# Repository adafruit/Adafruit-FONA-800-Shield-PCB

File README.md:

## Adafruit FONA 800 Shield PCB

<a href="http://www.adafruit.com/products/2468"><br/>
Click here to purchase one from the Adafruit shop</a>

PCB files for the Adafruit FONA 800 Shield. Format is EagleCAD schematic and board layout
* https://www.adafruit.com/products/2468

### DESCRIPTION
Ring, Ring! Who's that callin'? It's your microcontroller! Introducing Adafruit FONA 800 Shield, an adorable all-in-one cellular phone shield that lets you add voice, text, SMS and data to your project in an easy to use pluggable shield.

This shield fits on top of any classic Arduino or compatible, and packs a surprising amount of technology into it's little frame. At the heart is a GSM cellular module (we use the latest SIM800) the size of a postage stamp. This module can do just about everything. 

If you want a Shield Version with GPS, check out the Adafruit FONA 808 Shield - Mini Cellular GSM + GPS for Arduino [click here](https://www.adafruit.com/product/2636).

If you just want a plain FONA breakout, [click here](https://www.adafruit.com/product/1946).

Quad-band 850/900/1800/1900MHz - connect onto any global GSM network with any 2G SIM (in the USA, T-Mobile is suggested)
Make and receive voice calls using a headset OR an external 8Ω speaker + electret microphone
Send and receive SMS messages
Send and receive GPRS data (TCP/IP, HTTP, etc.)
Scan and receive FM radio broadcasts (yeah, we don't exactly know why this was included but it works really well)
PWM/Buzzer vibrational motor control
AT command interface with "auto baud" detection
Sounds delicious, right? So we plated this fine module onto a shield with all the extras you need to make your next project shine.

### License

Adafruit invests time and resources providing this open source design, please support Adafruit and open-source hardware by purchasing products from [Adafruit.com](https://www.adafruit.com)!

Designed by Adafruit Industries. 

Creative Commons Attribution, Share-Alike license, check license.txt for more information All text above must be included in any redistribution - 
See license.txt for more information.

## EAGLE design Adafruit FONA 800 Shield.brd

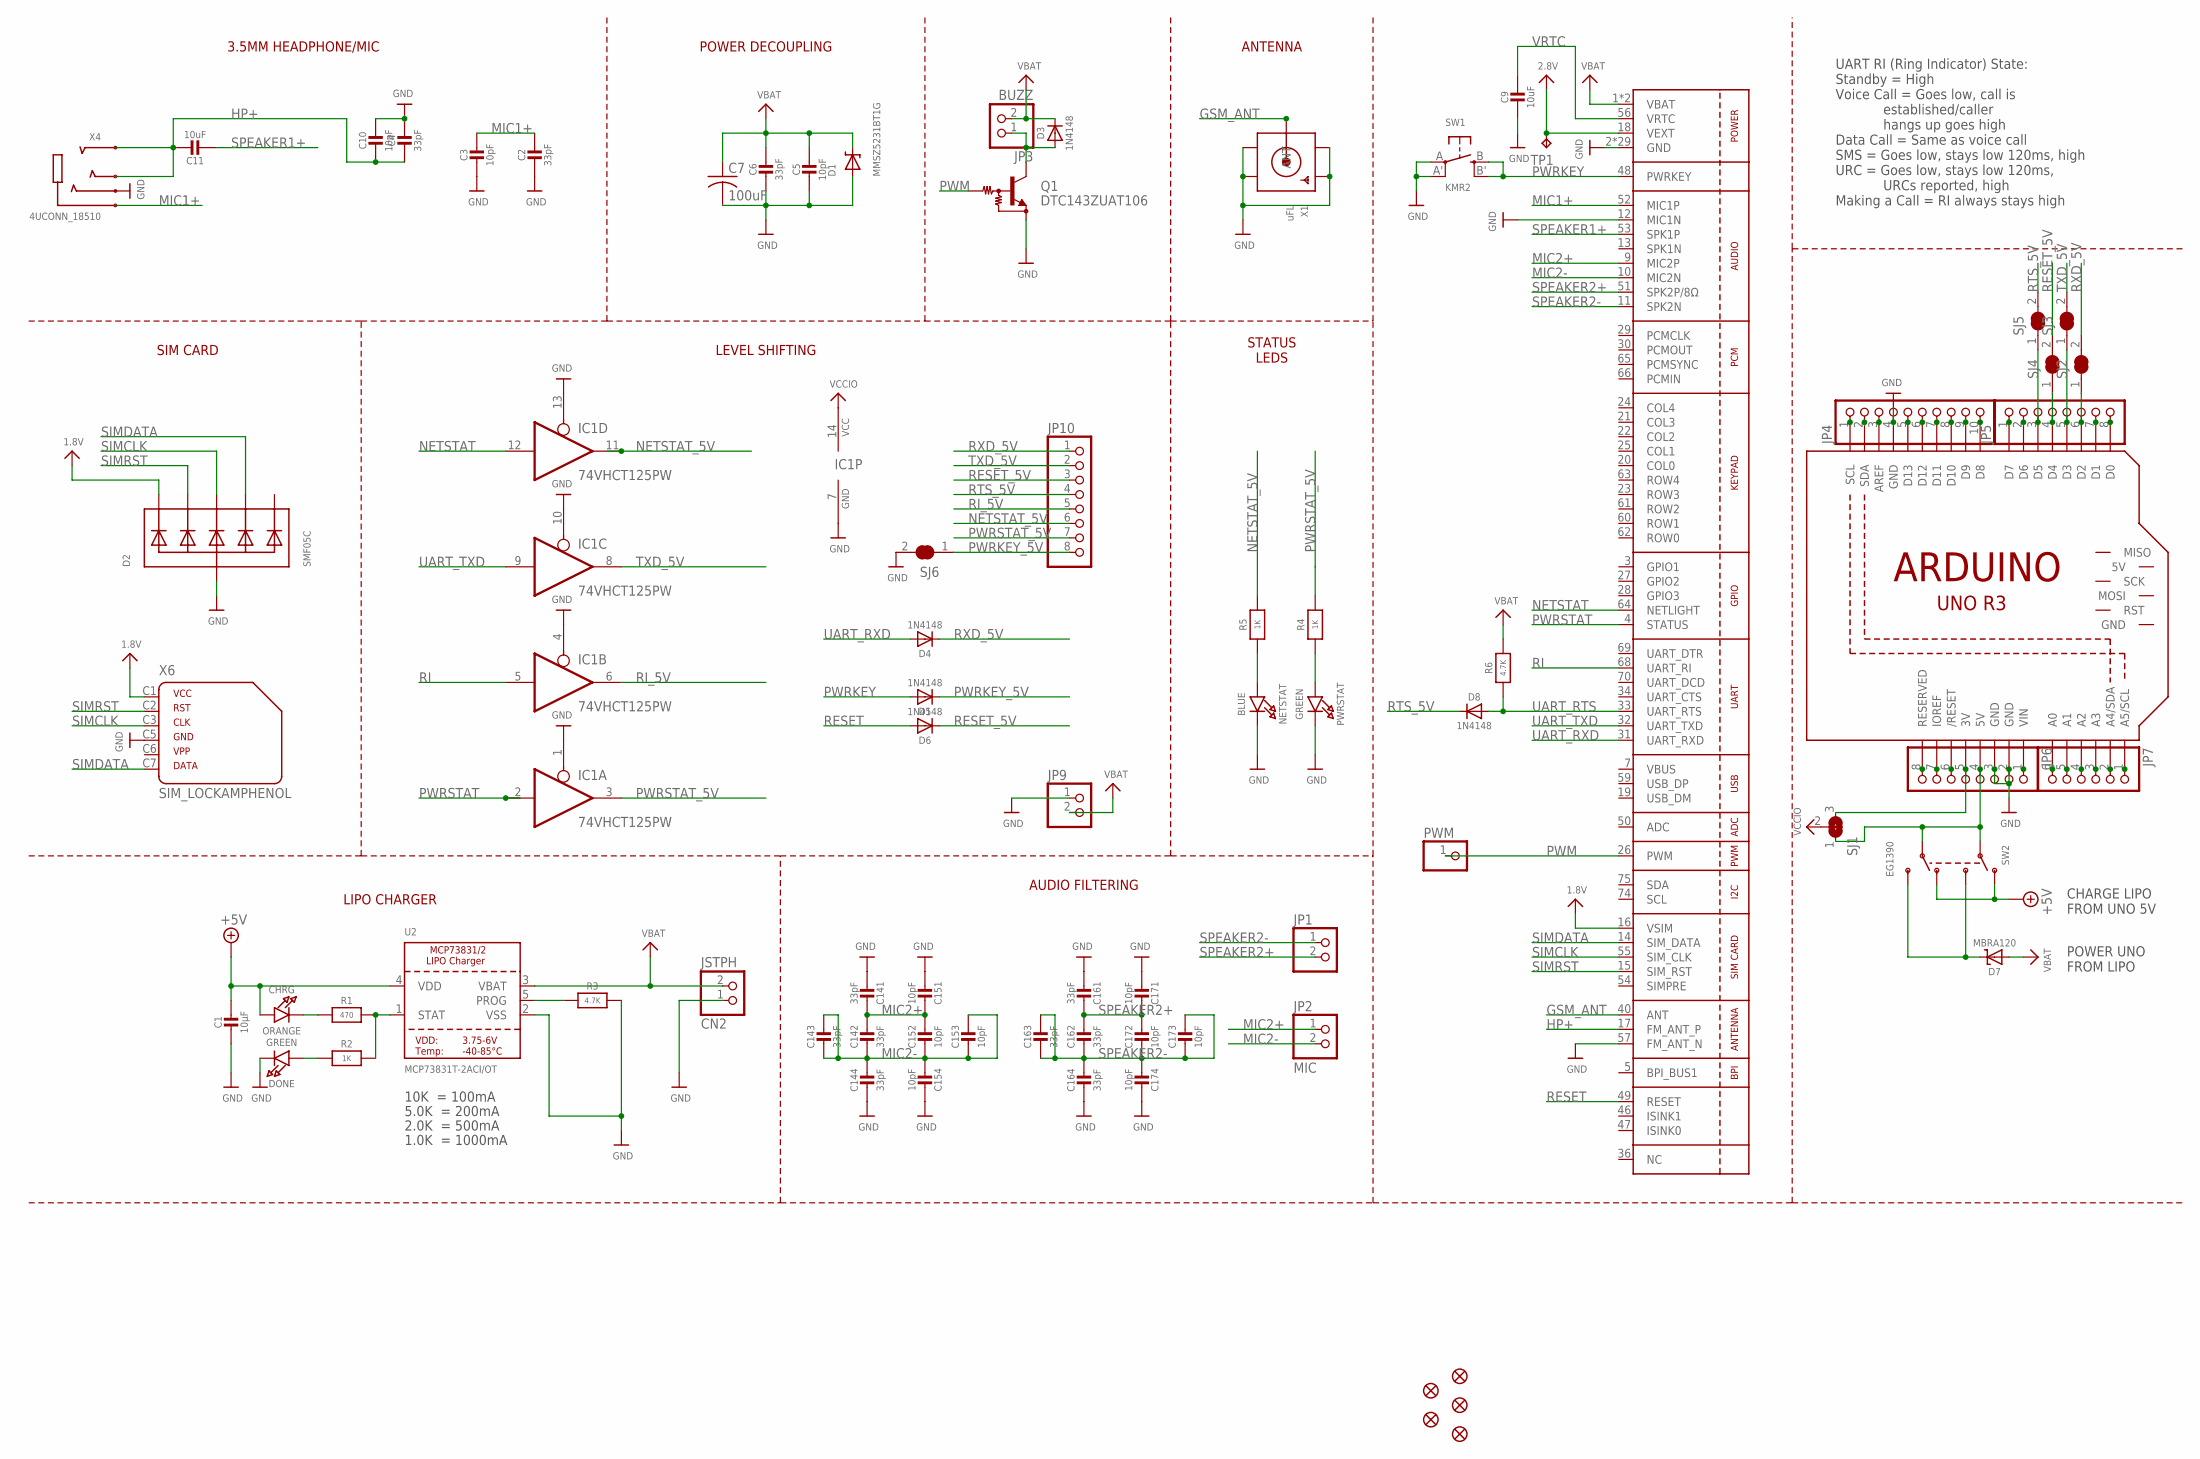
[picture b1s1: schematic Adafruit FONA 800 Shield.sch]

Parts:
C1: 10µF; 0805-NO
C2, C4, C6: 33pF; 0805-NO
C3, C5, C10: 10pF; 0805-NO
C7: 100uF; C1210
C9, C11: 10uF; 0805-NO
C14, C16: 33pF; RESPACK_4X0603
C15, C17: 10pF; RESPACK_4X0603
CHRG: ORANGE; CHIPLED_0805_NOOUTLINE
CN2: JSTPH; JSTPH2
D1: MMSZ5231BT1G; SOD-123
D2: SMF05C; SOT363
D3, D4, D5, D6, D8: 1N4148; SOD-323
D7: MBRA120; SOD-123
DONE: GREEN; CHIPLED_0805_NOOUTLINE
FID1, FID2, FID3, FID4, FID5: FIDUCIAL""; FIDUCIAL_1MM
IC1: 74VHCT125PW; TSSOP14
JP1, JP9: HEADER-1X2ROUND; 1X02_ROUND
JP2: MIC; 1X02_ROUND
JP3: BUZZ; 1X02_ROUND
JP4: HEADER-1X1070MIL; 1X10_ROUND70
JP5, JP6, JP10: HEADER-1X876MIL; 1X08_ROUND_76
JP7: HEADER-1X676MIL; 1X06_ROUND_76
M1: ARDUINO_R3_ICSP_NODIM; ARDUINOR3_ICSP_NODIM
NETSTAT: BLUE; CHIPLED_0805_NOOUTLINE
PWM: PINHD-1X1CB; 1X01-CLEANBIG
PWRSTAT: GREEN; CHIPLED_0805_NOOUTLINE
Q1: DTC143ZUAT106; SC59-BEC
R1: 470; 0805-NO
R2, R4, R5: 1K; 0805-NO
R3, R6: 4.7K; 0805-NO
SJ1: SOLDERJUMPER_2WAY; SOLDERJUMPER_2WAY_OPEN_NOPASTE
SJ2, SJ3, SJ4, SJ5, SJ6: SOLDERJUMPER_CLOSED; SOLDERJUMPER_CLOSEDWIRE
SW1: KMR2; EVQ-Q2
SW2: EG1390
TP1: TPTP11R; TP11R
U1: SIM800H/L; SIM800L
U2: MCP73831T-2ACI/OT; SOT23-5
X1: uFL; SMA_EDGELAUNCH_UFL
X4: 4UCONN_18510
X6: SIM_LOCKAMPHENOL; C707_10M006_512_2

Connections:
1.8V: D2.1 (C1), U1.16 (VSIM), X6.C1 (1)
2.8V: TP1.TP, U1.18 (VEXT)
3V: JP6.5, M1.3V, SJ1.3
5V: JP6.4, M1.5V, SJ1.1, SW2.P1, SW2.P2
+5V: C1.1, CHRG.A, SW2.O1, SW2.O2, U2.4 (VDD)
A0: JP7.6, M1.A0
A1: JP7.5, M1.A1
A2: JP7.4, M1.A2
A3: JP7.3, M1.A3
A4: JP7.2, M1.A4 (A4/SDA)
A5: JP7.1, M1.A5 (A5/SCL)
AREF: JP4.3, M1.AREF
BUZZ-: D3.A, JP3.1, Q1.C
D0: JP5.8, M1.D0
D1: JP5.7, M1.D1
D2: JP5.6, M1.D2, SJ2.1
D3: JP5.5, M1.D3, SJ3.1
D4: JP5.4, M1.D4, SJ4.1
D5: JP5.3, M1.D5, SJ5.1
D6: JP5.2, M1.D6
D7: JP5.1, M1.D7
D8: JP4.10, M1.D8
D9: JP4.9, M1.D9
D10: JP4.8, M1.D10
D11: JP4.7, M1.D11
D12: JP4.6, M1.D12
D13: JP4.5, M1.D13
GND: C1.2, C2.2, C3.2, C4.1, C5.2, C6.2, C7.2, C9.2, C10.1, C14.5 (2), C14.8 (2), C15.4 (1), C15.8 (2), C16.5 (2), C16.8 (2), C17.4 (1), C17.8 (2), CN2.1, D1.A, D2.2 (A), DONE.C, IC1.1 (OE), IC1.4 (OE), IC1.7 (GND), IC1.10 (OE), IC1.13 (OE), JP4.4, JP6.2, JP6.3, JP9.1, M1.GND, M1.GND@1 (GND), M1.GND@3 (GND), NETSTAT.C, PWRSTAT.C, Q1.E, R3.2, SJ6.2, SW1.A, SW1.A' (P1), U1.2 (GND), U1.6 (GND), U1.8 (GND), U1.12 (MIC1N), U1.35 (GND), U1.37 (GND), U1.38 (GND), U1.39 (GND), U1.41 (GND), U1.43 (GND), U1.44 (GND), U1.45 (GND), U1.57 (FM_ANT_N), U1.58 (GND), U1.67 (GND), U1.71 (GND), U1.72 (GND), U1.73 (GND), U1.76 (GND), U1.77 (GND), U1.78 (GND), U1.79 (GND), U1.80 (GND), U1.81 (GND), U1.82 (GND), U1.83 (GND), U1.84 (GND), U1.85 (GND), U1.86 (GND), U1.87 (GND), U1.88 (GND), U2.2 (VSS), X1.GND@1 (GND1), X1.GND@2 (GND2), X1.GND@3 (GND3), X1.GND@4 (GND4), X4.4-INNER_SLEEVE (RING1), X6.C5 (4)
GSM_ANT: U1.40 (ANT), X1.P (ANT)
HP+: C4.2, C10.2, C11.1, U1.17 (FM_ANT_P), X4.2-TIP (RING3), X4.3-OUTER_SLEEVE (RING2)
IOREF: JP6.7, M1.IOREF
MIC1+: C2.1, C3.1, U1.52 (MIC1P), X4.1-GND (TIP)
MIC2+: C14.1, C14.2 (1), C15.1, C15.2 (1), JP2.1, U1.9 (MIC2P)
MIC2-: C14.3 (1), C14.4 (1), C14.6 (2), C14.7 (2), C15.3 (1), C15.5 (2), C15.6 (2), C15.7 (2), JP2.2, U1.10 (MIC2N)
unnamed: CHRG.C, R1.1
unnamed: R1.2, R2.2, U2.1 (STAT)
unnamed: PWRSTAT.A, R4.1
unnamed: R3.1, U2.5 (PROG)
unnamed: DONE.A, R2.1
unnamed: D7.C, SW2.S1, SW2.S2
unnamed: NETSTAT.A, R5.1
NC: JP6.8, M1.RESERVED
NETSTAT: IC1.12 (I), U1.64 (NETLIGHT)
NETSTAT_5V: IC1.11 (O), JP10.6, R5.2
PWM: PWM.1, Q1.B, U1.26 (PWM)
PWRKEY: D5.A, SW1.B (S), SW1.B' (S1), U1.48 (PWRKEY)
PWRKEY_5V: D5.C, JP10.8, SJ6.1
PWRSTAT: IC1.2 (I), U1.4 (STATUS)
PWRSTAT_5V: IC1.3 (O), JP10.7, R4.2
RESET: D6.A, U1.49 (RESET)
RESET_5V: D6.C, JP10.3, SJ4.2
RI: IC1.5 (I), U1.68 (UART_RI)
RI_5V: IC1.6 (O), JP10.5
RST: JP6.6, M1.RESET (/RESET)
RTS_5V: D8.C, JP10.4, SJ5.2
RXD_5V: D4.C, JP10.1, SJ2.2
SCL: JP4.1, M1.SCL
SDA: JP4.2, M1.SDA
SIMCLK: D2.4 (C3), U1.55 (SIM_CLK), X6.C3 (3)
SIMDATA: D2.5 (C4), U1.14 (SIM_DATA), X6.C7 (6)
SIMRST: D2.3 (C2), U1.15 (SIM_RST), X6.C2 (2)
SPEAKER1+: C11.2, U1.53 (SPK1P)
SPEAKER2+: C16.1, C16.2 (1), C17.1, C17.2 (1), JP1.2, U1.51 (SPK2P/8Ω)
SPEAKER2-: C16.3 (1), C16.4 (1), C16.6 (2), C16.7 (2), C17.3 (1), C17.5 (2), C17.6 (2), C17.7 (2), JP1.1, U1.11 (SPK2N)
TXD_5V: IC1.8 (O), JP10.2, SJ3.2
UART_RTS: D8.A, R6.1, U1.33 (UART_RTS)
UART_RXD: D4.A, U1.31 (UART_RXD)
UART_TXD: IC1.9 (I), U1.32 (UART_TXD)
VBAT: C5.1, C6.1, C7.1, CN2.2, D1.C, D3.C, D7.A, JP3.2, JP9.2, R6.2, U1.1 (VBAT), U1.42 (VBAT), U2.3 (VBAT)
VBUS: U1.7 (VBUS)
VCCIO: IC1.14 (VCC), SJ1.2
VIN: JP6.1, M1.VIN
VRTC: C9.1, U1.56 (VRTC)

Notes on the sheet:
10K = 100mA
5.0K = 200mA
2.0K = 500mA
1.0K = 1000mA
UART RI (Ring Indicator) State: Standby = High Voice Call = Goes low, call is established/caller hangs up goes high Data Call = Same as voice call SMS = Goes low, stays low 120ms, high URC = Goes low, stays low 120ms, URCs reported, high Making a Call = RI always stays high
ANTENNA
POWER DECOUPLING
3.5MM HEADPHONE/MIC
SIM CARD
LEVEL SHIFTING
LIPO CHARGER
AUDIO FILTERING
STATUS LEDS
CHARGE LIPO FROM UNO 5V
POWER UNO FROM LIPO

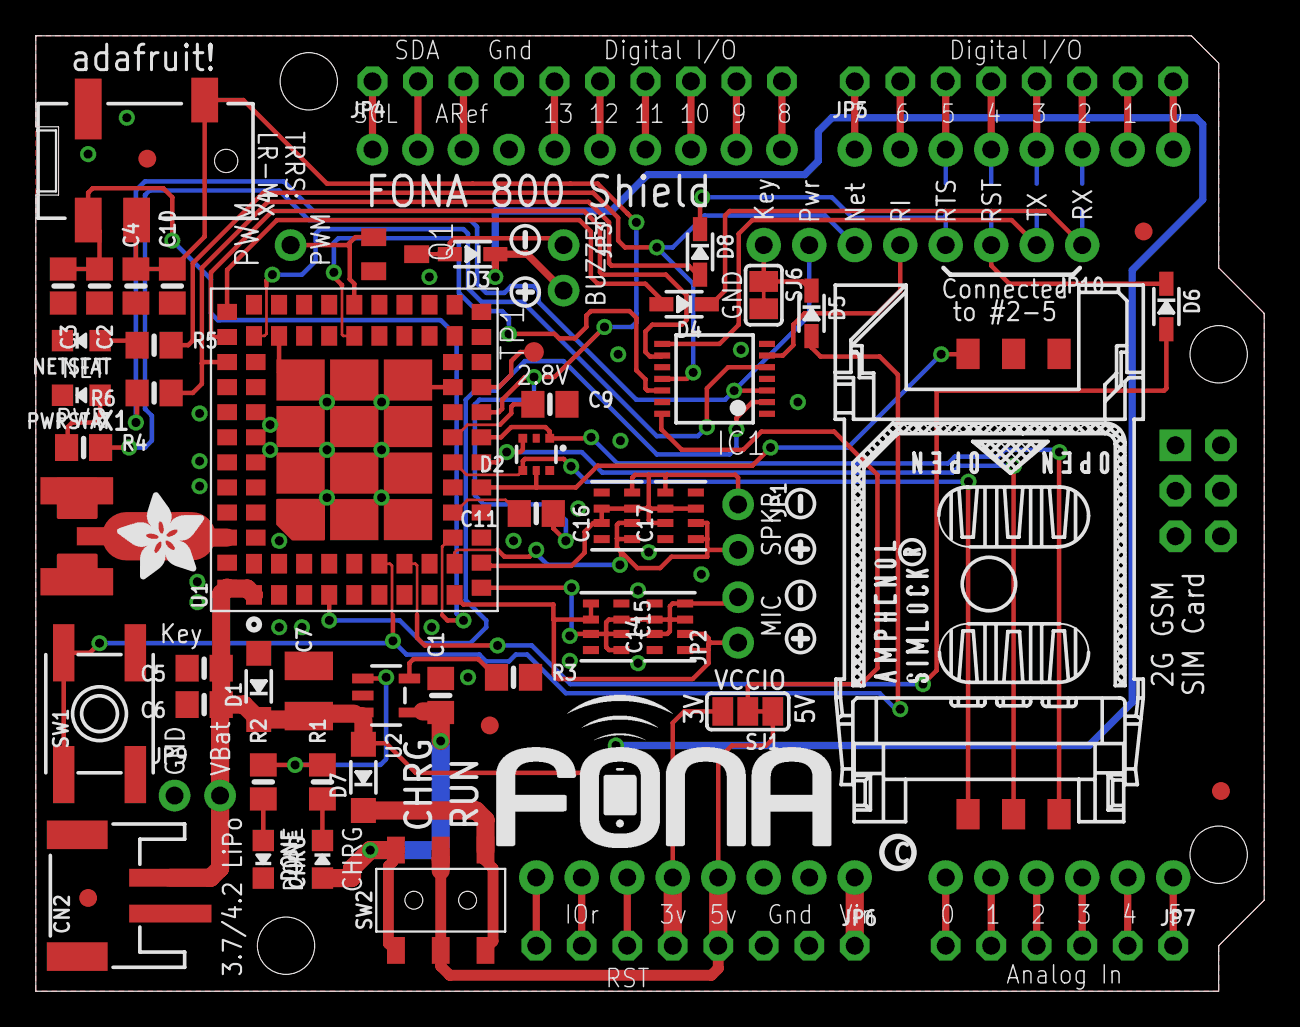
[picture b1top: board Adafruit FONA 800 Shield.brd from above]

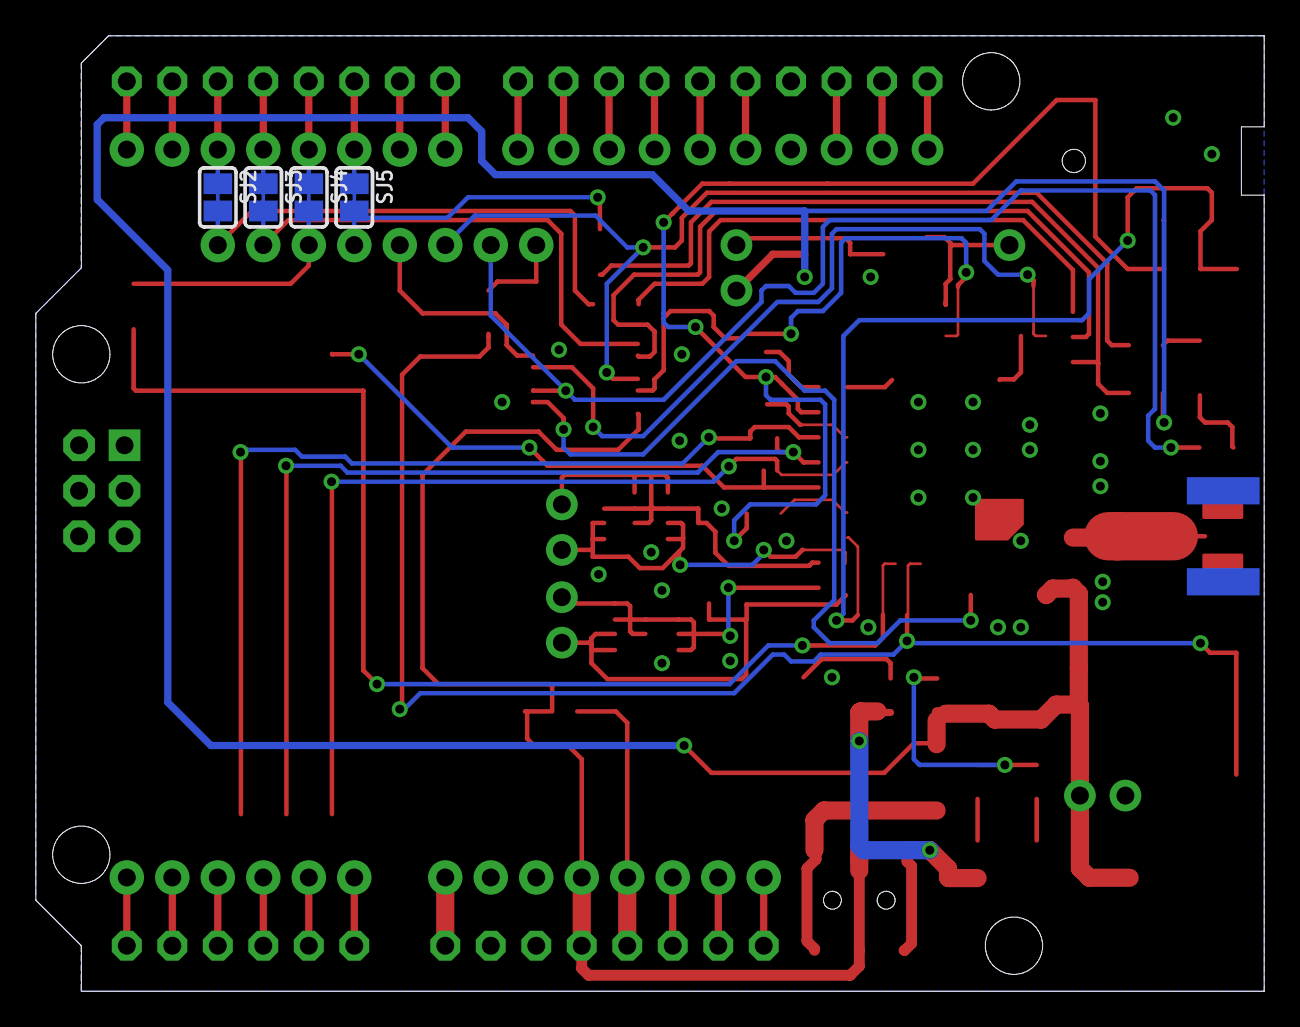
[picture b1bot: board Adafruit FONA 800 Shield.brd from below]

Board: 2 copper layers, 68.6 x 53.3 mm, 74 parts (4 on the bottom side), 72 nets.

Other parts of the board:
U$2, U$36, U$43: SYMBOL_PLUS
U$10: ADAFRUIT_5MM
U$26: FONA_LOGO
U$33, U$34, U$57: SYMBOL_MINUS
U$59: PCBFEAT-REV-040

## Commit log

2016-09-30 init

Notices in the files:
parts and their libraries:
microbuilder: This work is placed in the public domain, and may be freely used for commercial and non-commercial work with the following conditions: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
